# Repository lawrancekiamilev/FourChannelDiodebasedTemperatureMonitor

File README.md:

# FourChannelDiodebasedTemperatureMonitor
this project is a pcb and programing project. it is designed to be able to read the temperature of any diode based on its non ideal diode factor.  It is also designed to read an i2c EEPROM for serial identification and incorporates itself with a gui

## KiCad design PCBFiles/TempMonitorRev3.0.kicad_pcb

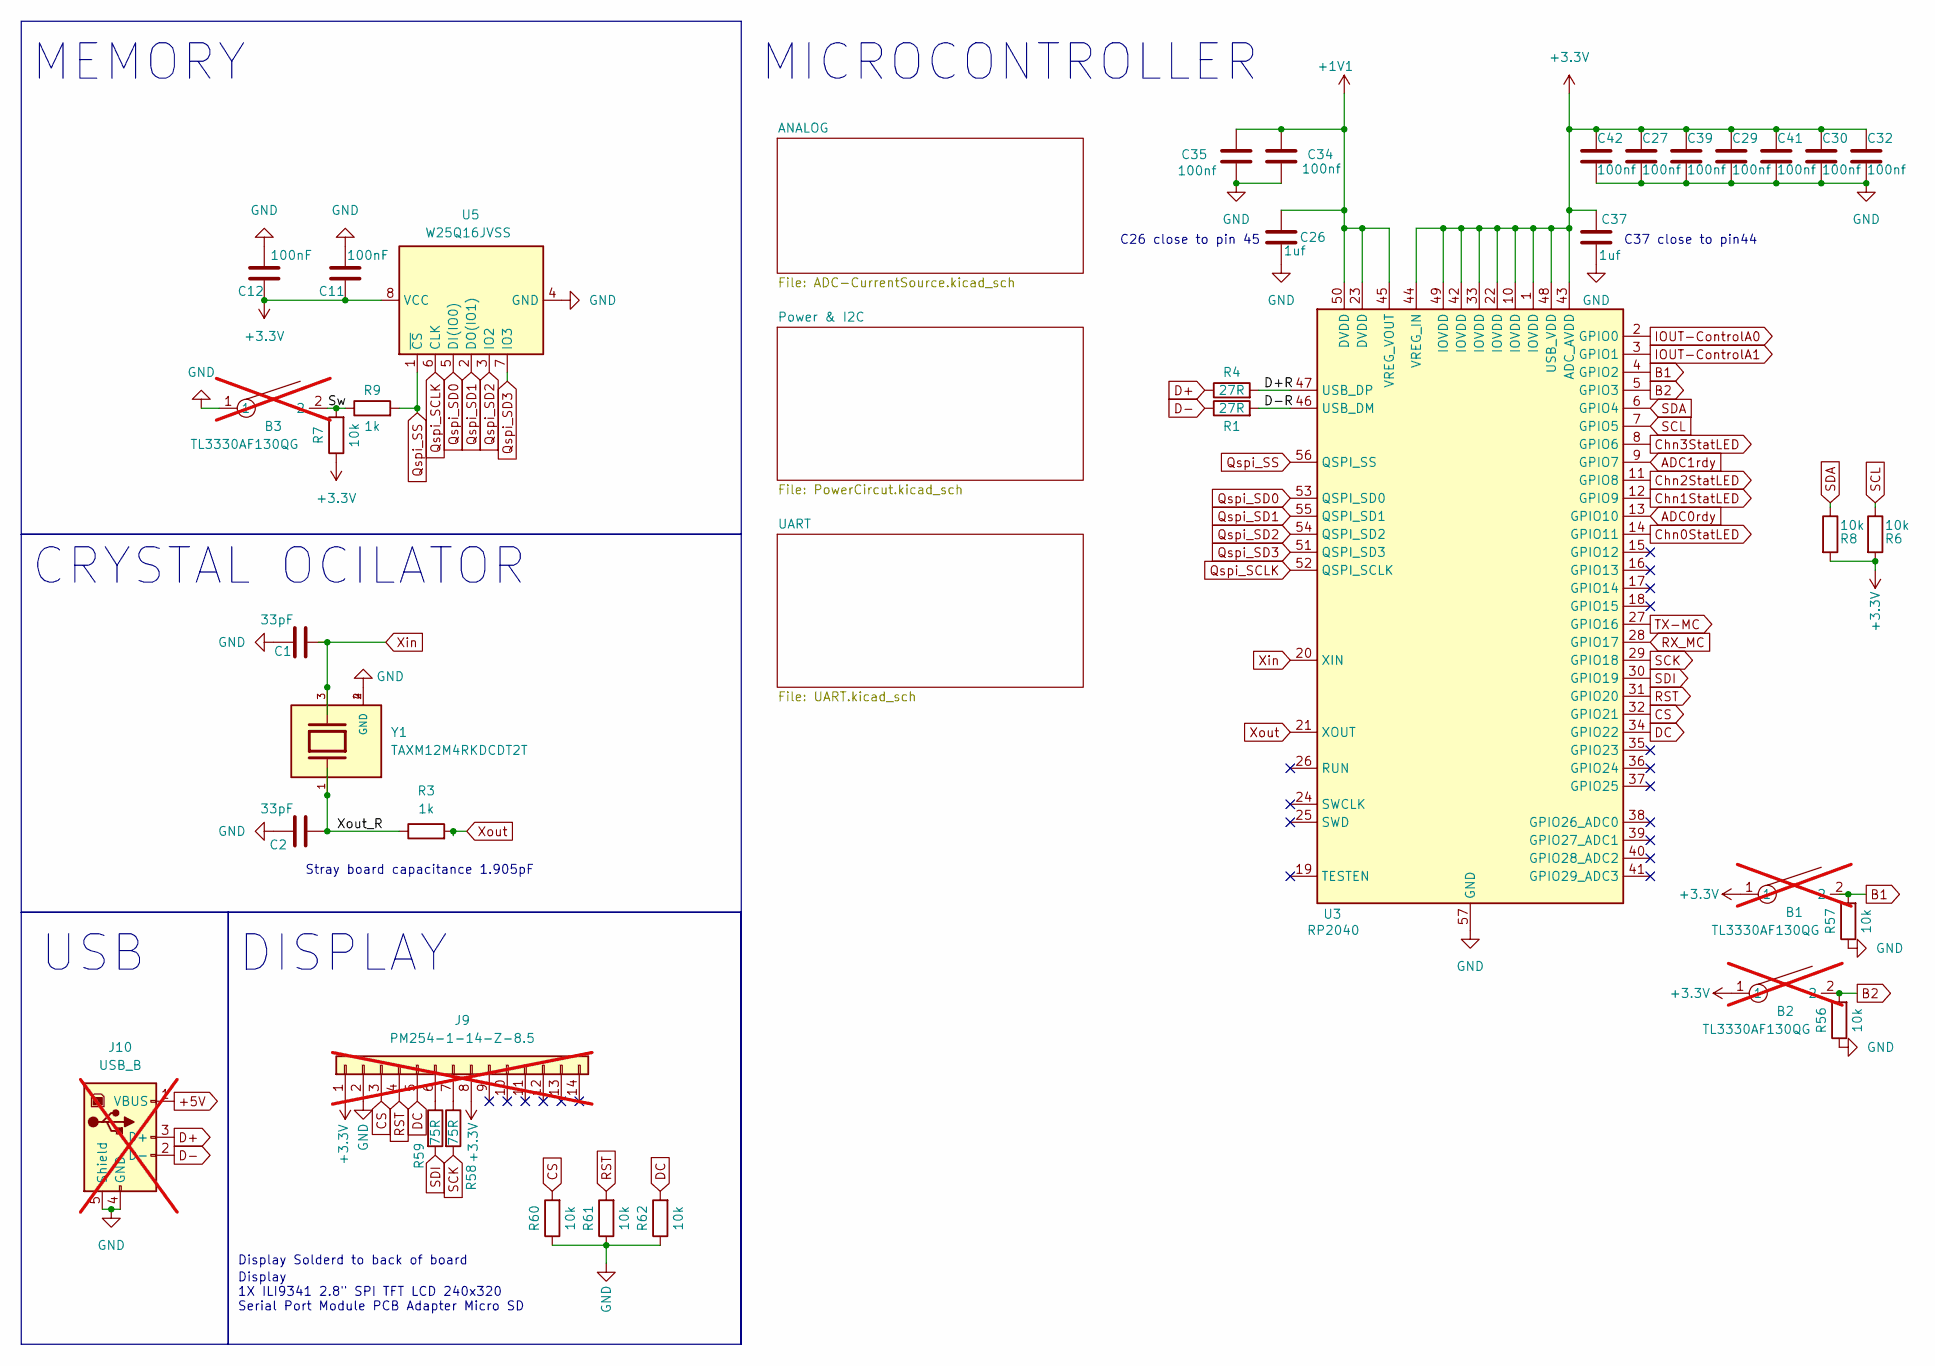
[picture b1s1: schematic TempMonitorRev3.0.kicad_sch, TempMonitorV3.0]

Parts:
B1, B2, B3: TL3330AF130QG; TL3330; JLC part # C2886885; not fitted
C1, C2: 33pF; C_0603_1608Metric; JLC part # C107047
C11, C12: 100nF; C_0603_1608Metric; JLC part # C14663
C26, C37: 1uf; C_0603_1608Metric; JLC part # C15849
C27, C29, C30, C32, C34, C35, C39, C41, C42: 100nf; C_0603_1608Metric; JLC part # C14663
J9: PM254-1-14-Z-8.5; PinSocket_1x14_P2.54mm_Vertical; JLC part # C2897377; not fitted
J10: USB_B; USB_B_OST_USB-B1HSxx_Horizontal; JLC part # C46392; not fitted
R1, R4: 27R; R_0603_1608Metric; JLC part # C25190
R3, R9: 1k; R_0603_1608Metric; JLC part # C21190
R6, R7, R8, R56, R57, R60, R61, R62: 10k; R_0603_1608Metric; JLC part # C25804
R58, R59: 75R; R_0603_1608Metric; JLC part # C25133
U3: RP2040; QFN-56-1EP_7x7mm_P0.4mm_EP3.2x3.2mm_ThermalVias; JLC part # C2040
U5: W25Q16JVSS; SOIC-8_5.3x5.3mm_P1.27mm; JLC part # C131025
Y1: TAXM12M4RKDCDT2T; Crystal_SMD_3225-4Pin_3.2x2.5mm; JLC part # C403945

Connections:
+1V1: C26.2, C34.1, C35.1, U3.23 (DVDD), U3.45 (VREG_VOUT), U3.50 (DVDD)
+3.3V: B1.1, B2.1, C11.1, C12.1, C27.1, C29.1, C30.1, C32.1, C37.2, C39.1, C41.1, C42.1, J9.1, J9.8, R6.2, R7.1, R8.2, U3.1 (IOVDD), U3.10 (IOVDD), U3.22 (IOVDD), U3.33 (IOVDD), U3.42 (IOVDD), U3.43 (ADC_AVDD), U3.44 (VREG_IN), U3.48 (USB_VDD), U3.49 (IOVDD), U5.8 (VCC); also elsewhere on the board
+5V: J10.1 (VBUS); also elsewhere on the board
/D+R: R4.2, U3.47 (USB_DP)
/D-R: R1.2, U3.46 (USB_DM)
/Sw: B3.2, R7.2, R9.1
/Xout_R: C2.1, R3.1, Y1.1
ADC0rdy: U3.13 (GPIO10); also elsewhere on the board
ADC1rdy: U3.9 (GPIO7); also elsewhere on the board
B1: B1.2, R57.2, U3.4 (GPIO2)
B2: B2.2, R56.2, U3.5 (GPIO3)
CS: J9.3, R60.2, U3.32 (GPIO21)
Chn0StatLED: U3.14 (GPIO11); also elsewhere on the board
Chn1StatLED: U3.12 (GPIO9); also elsewhere on the board
Chn2StatLED: U3.11 (GPIO8); also elsewhere on the board
Chn3StatLED: U3.8 (GPIO6); also elsewhere on the board
D+: J10.3 (D+), R4.1
D-: J10.2 (D-), R1.1
DC: J9.5, R62.2, U3.34 (GPIO22)
GND: B3.1, C1.2, C2.2, C11.2, C12.2, C26.1, C27.2, C29.2, C30.2, C32.2, C34.2, C35.2, C37.1, C39.2, C41.2, C42.2, J9.2, J10.4 (GND), J10.5 (Shield), R56.1, R57.1, R60.1, R61.1, R62.1, U3.57 (GND), U5.4 (GND), Y1.2 (GND), Y1.4 (GND); also elsewhere on the board
IOUT-ControlA0: U3.2 (GPIO0); also elsewhere on the board
IOUT-ControlA1: U3.3 (GPIO1); also elsewhere on the board
unnamed: J9.6, R59.1
unnamed: J9.7, R58.1
Qspi_SCLK: U3.52 (QSPI_SCLK), U5.6 (CLK)
Qspi_SD0: U3.53 (QSPI_SD0), U5.5 (DI(IO0))
Qspi_SD1: U3.55 (QSPI_SD1), U5.2 (DO(IO1))
Qspi_SD2: U3.54 (QSPI_SD2), U5.3 (IO2)
Qspi_SD3: U3.51 (QSPI_SD3), U5.7 (IO3)
Qspi_SS: R9.2, U3.56 (QSPI_SS), U5.1 (~CS)
RST: J9.4, R61.2, U3.31 (GPIO20)
RX_MC: U3.28 (GPIO17); also elsewhere on the board
SCK: R58.2, U3.29 (GPIO18)
SCL: R6.1, U3.7 (GPIO5); also elsewhere on the board
SDA: R8.1, U3.6 (GPIO4); also elsewhere on the board
SDI: R59.2, U3.30 (GPIO19)
TX-MC: U3.27 (GPIO16); also elsewhere on the board
Xin: C1.1, U3.20 (XIN), Y1.3
Xout: R3.2, U3.21 (XOUT)

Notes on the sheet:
C37 close to pin44
CRYSTAL OCILATOR
MICROCONTROLLER
Stray board capacitance 1.905pF
MEMORY
DISPLAY
Display 1X ILI9341 2.8" SPI TFT LCD 240x320 Serial Port Module PCB Adapter Micro SD
Display Solderd to back of board
USB
C26 close to pin 45

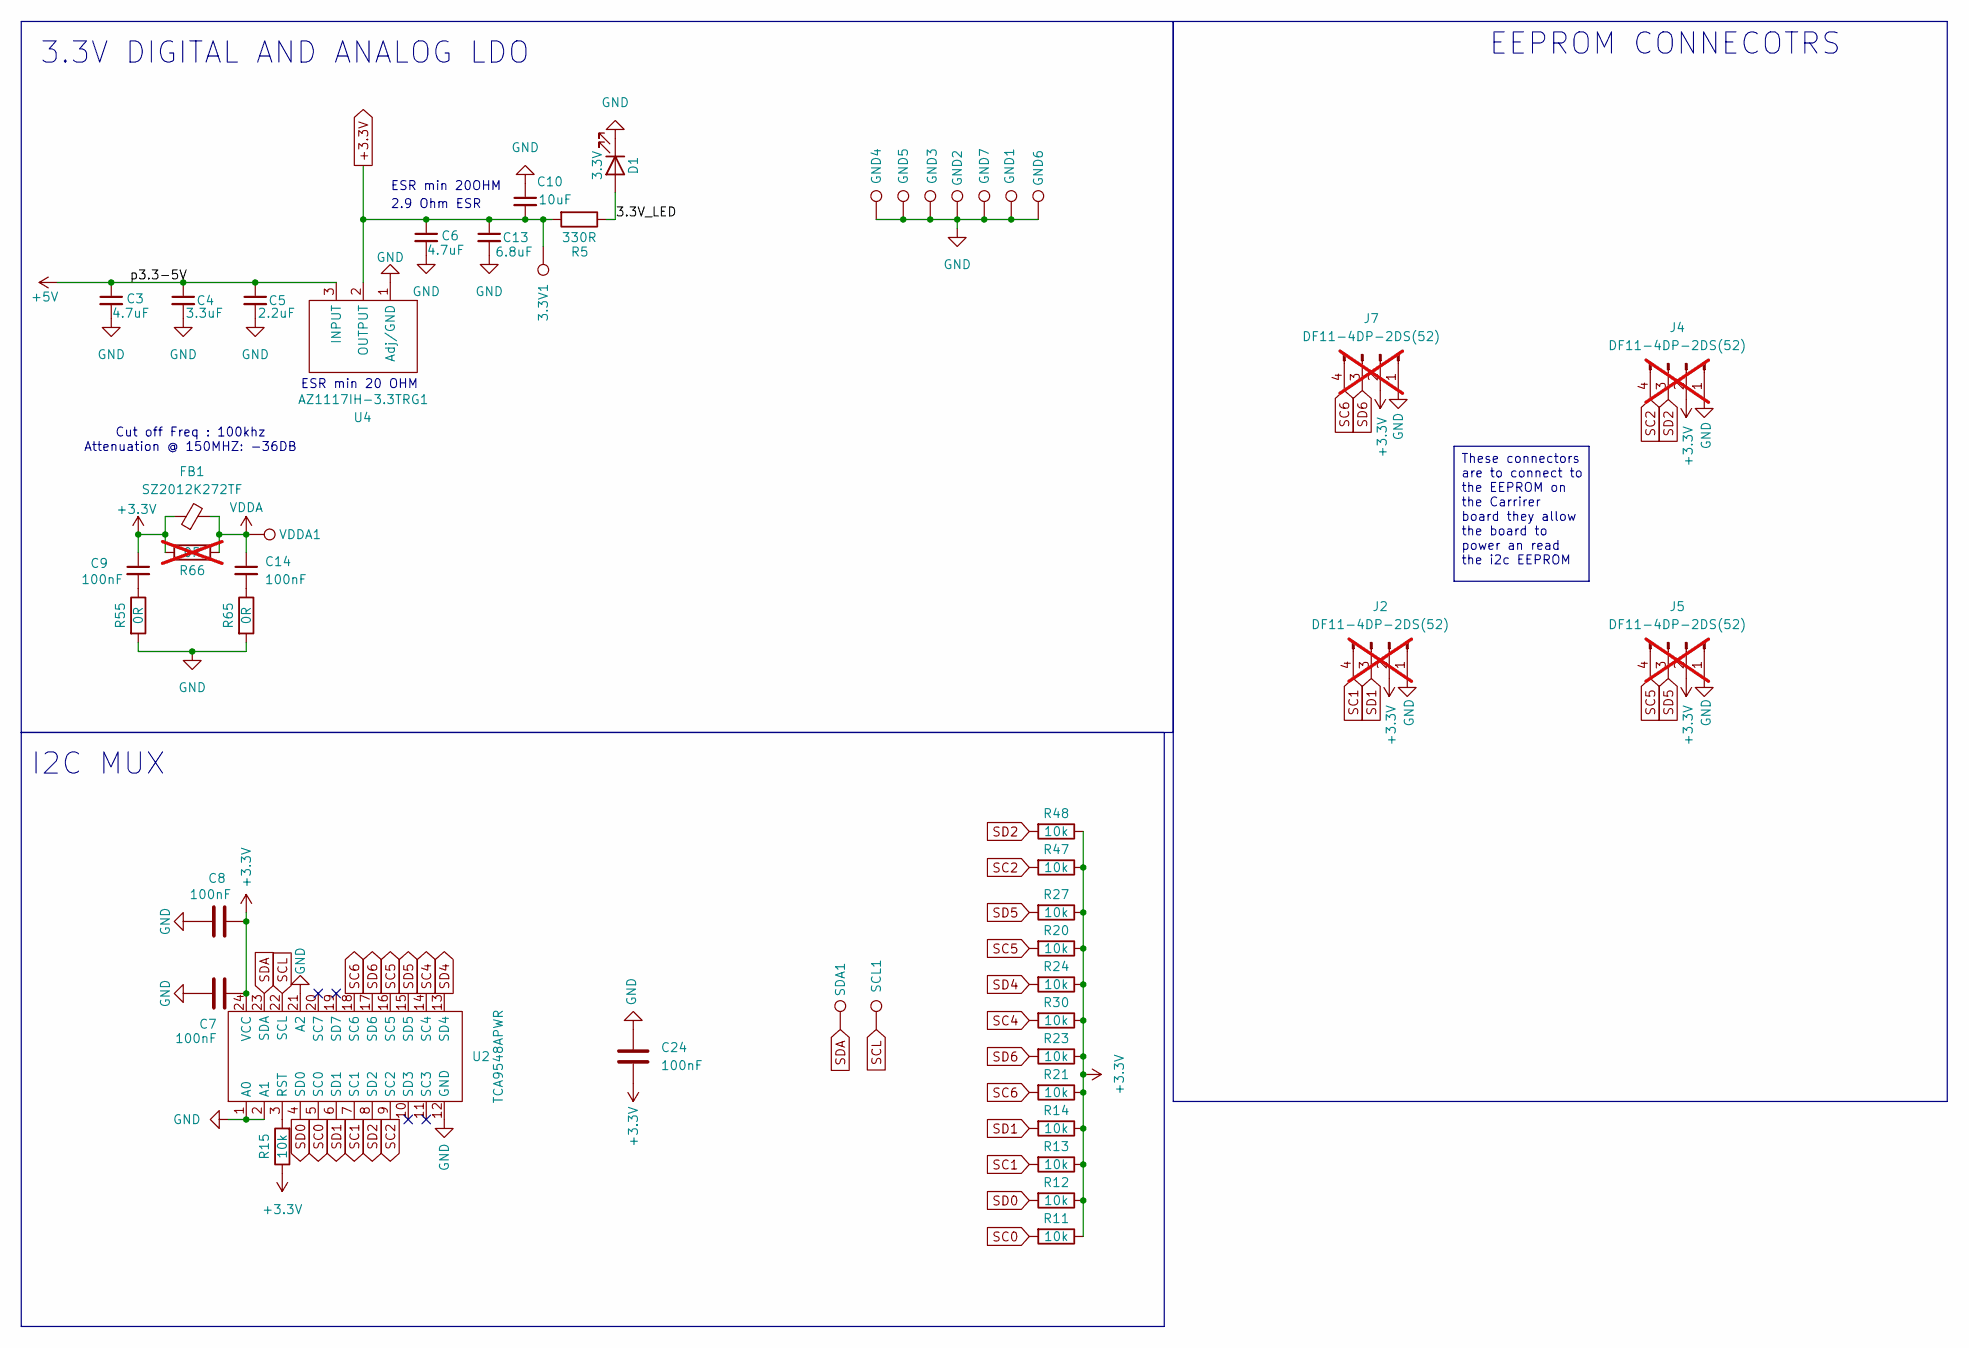
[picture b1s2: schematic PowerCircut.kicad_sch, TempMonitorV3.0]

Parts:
3.3V1: TestPoint; TestPoint_Pad_D1.5mm
C3, C6: 4.7uF; C_0805_2012Metric; JLC part # C1779
C4: 3.3uF; C_0805_2012Metric; JLC part # C7393948
C5: 2.2uF; C_0805_2012Metric; JLC part # C19110
C7, C8, C24: 100nF; C_0603_1608Metric; JLC part # C14663
C9, C14: 100nF; C_0805_2012Metric; JLC part # C49678
C10: 10uF; C_0805_2012Metric; JLC part # C5139488
C13: 6.8uF; C_0805_2012Metric; JLC part # C15850
D1: 3.3V; LED_0603_1608Metric_Pad1.05x0.95mm_HandSolder; JLC part # C19171390
FB1: SZ2012K272TF; R_0805_2012Metric; JLC part # C185876
GND1, GND2, GND3, GND4, GND5, GND6, GND7: TestPoint; TestPoint_Pad_D1.5mm
J2, J4, J5, J7: DF11-4DP-2DS(52); HRS_DF11-4DP-2DS_52_; not fitted
R5: 330R; R_0603_1608Metric; JLC part # C22775
R11, R12, R13, R14, R15, R20, R21, R23, R24, R27, R30, R47, R48: 10k; R_0603_1608Metric; JLC part # C25804
R55, R65: 0R; R_0603_1608Metric; JLC part # C21189
R66: 0R; R_0603_1608Metric; JLC part # C25804; not fitted
SCL1: TestPoint; TestPoint_Pad_D1.5mm
SDA1: TestPoint; TestPoint_Pad_D1.5mm
U2: TCA9548APWR; TCA9548A; JLC part # C130026
U4: AZ1117IH-3.3TRG1; AZ11171; JLC part # C108495
VDDA1: TestPoint; TestPoint_Pad_D1.5mm

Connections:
+3.3V: 3.3V1.1, C6.1, C7.2, C8.2, C9.1, C10.2, C13.1, C24.2, FB1.1, J2.2, J4.2, J5.2, J7.2, R5.2, R11.1, R12.1, R13.1, R14.1, R15.1, R20.1, R21.1, R23.1, R24.1, R27.1, R30.1, R47.1, R48.1, R66.1, U2.24 (VCC), U4.2 (OUTPUT); also elsewhere on the board
+5V: C3.1, C4.1, C5.1, U4.3 (INPUT); also elsewhere on the board
/Power & I2C/3.3V_LED: D1.2 (A), R5.1
GND: C3.2, C4.2, C5.2, C6.2, C7.1, C8.1, C10.1, C13.2, C24.1, D1.1 (K), GND1.1, GND2.1, GND3.1, GND4.1, GND5.1, GND6.1, GND7.1, J2.1, J4.1, J5.1, J7.1, R55.2, R65.2, U2.1 (A0), U2.2 (A1), U2.12 (GND), U2.21 (A2), U4.1 (Adj/GND); also elsewhere on the board
unnamed: C9.2, R55.1
unnamed: C14.2, R65.1
unnamed: R15.2, U2.3 (RST)
SC0: R11.2, U2.5 (SC0); also elsewhere on the board
SC1: J2.4, R13.2, U2.7 (SC1)
SC2: J4.4, R47.2, U2.9 (SC2)
SC4: R30.2, U2.14 (SC4); also elsewhere on the board
SC5: J5.4, R20.2, U2.16 (SC5)
SC6: J7.4, R21.2, U2.18 (SC6)
SCL: SCL1.1, U2.22 (SCL); also elsewhere on the board
SD0: R12.2, U2.4 (SD0); also elsewhere on the board
SD1: J2.3, R14.2, U2.6 (SD1)
SD2: J4.3, R48.2, U2.8 (SD2)
SD4: R24.2, U2.13 (SD4); also elsewhere on the board
SD5: J5.3, R27.2, U2.15 (SD5)
SD6: J7.3, R23.2, U2.17 (SD6)
SDA: SDA1.1, U2.23 (SDA); also elsewhere on the board
VDDA: C14.1, FB1.2, R66.2, VDDA1.1; also elsewhere on the board

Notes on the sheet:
Cut off Freq : 100khz Attenuation @ 150MHZ: -36DB
I2C MUX
3.3V DIGITAL AND ANALOG LDO
ESR min 20 OHM
2.9 Ohm ESR
EEPROM CONNECOTRS
ESR min 20OHM
These connectors are to connect to the EEPROM on the Carrirer board they allow the board to power an read the i2c EEPROM

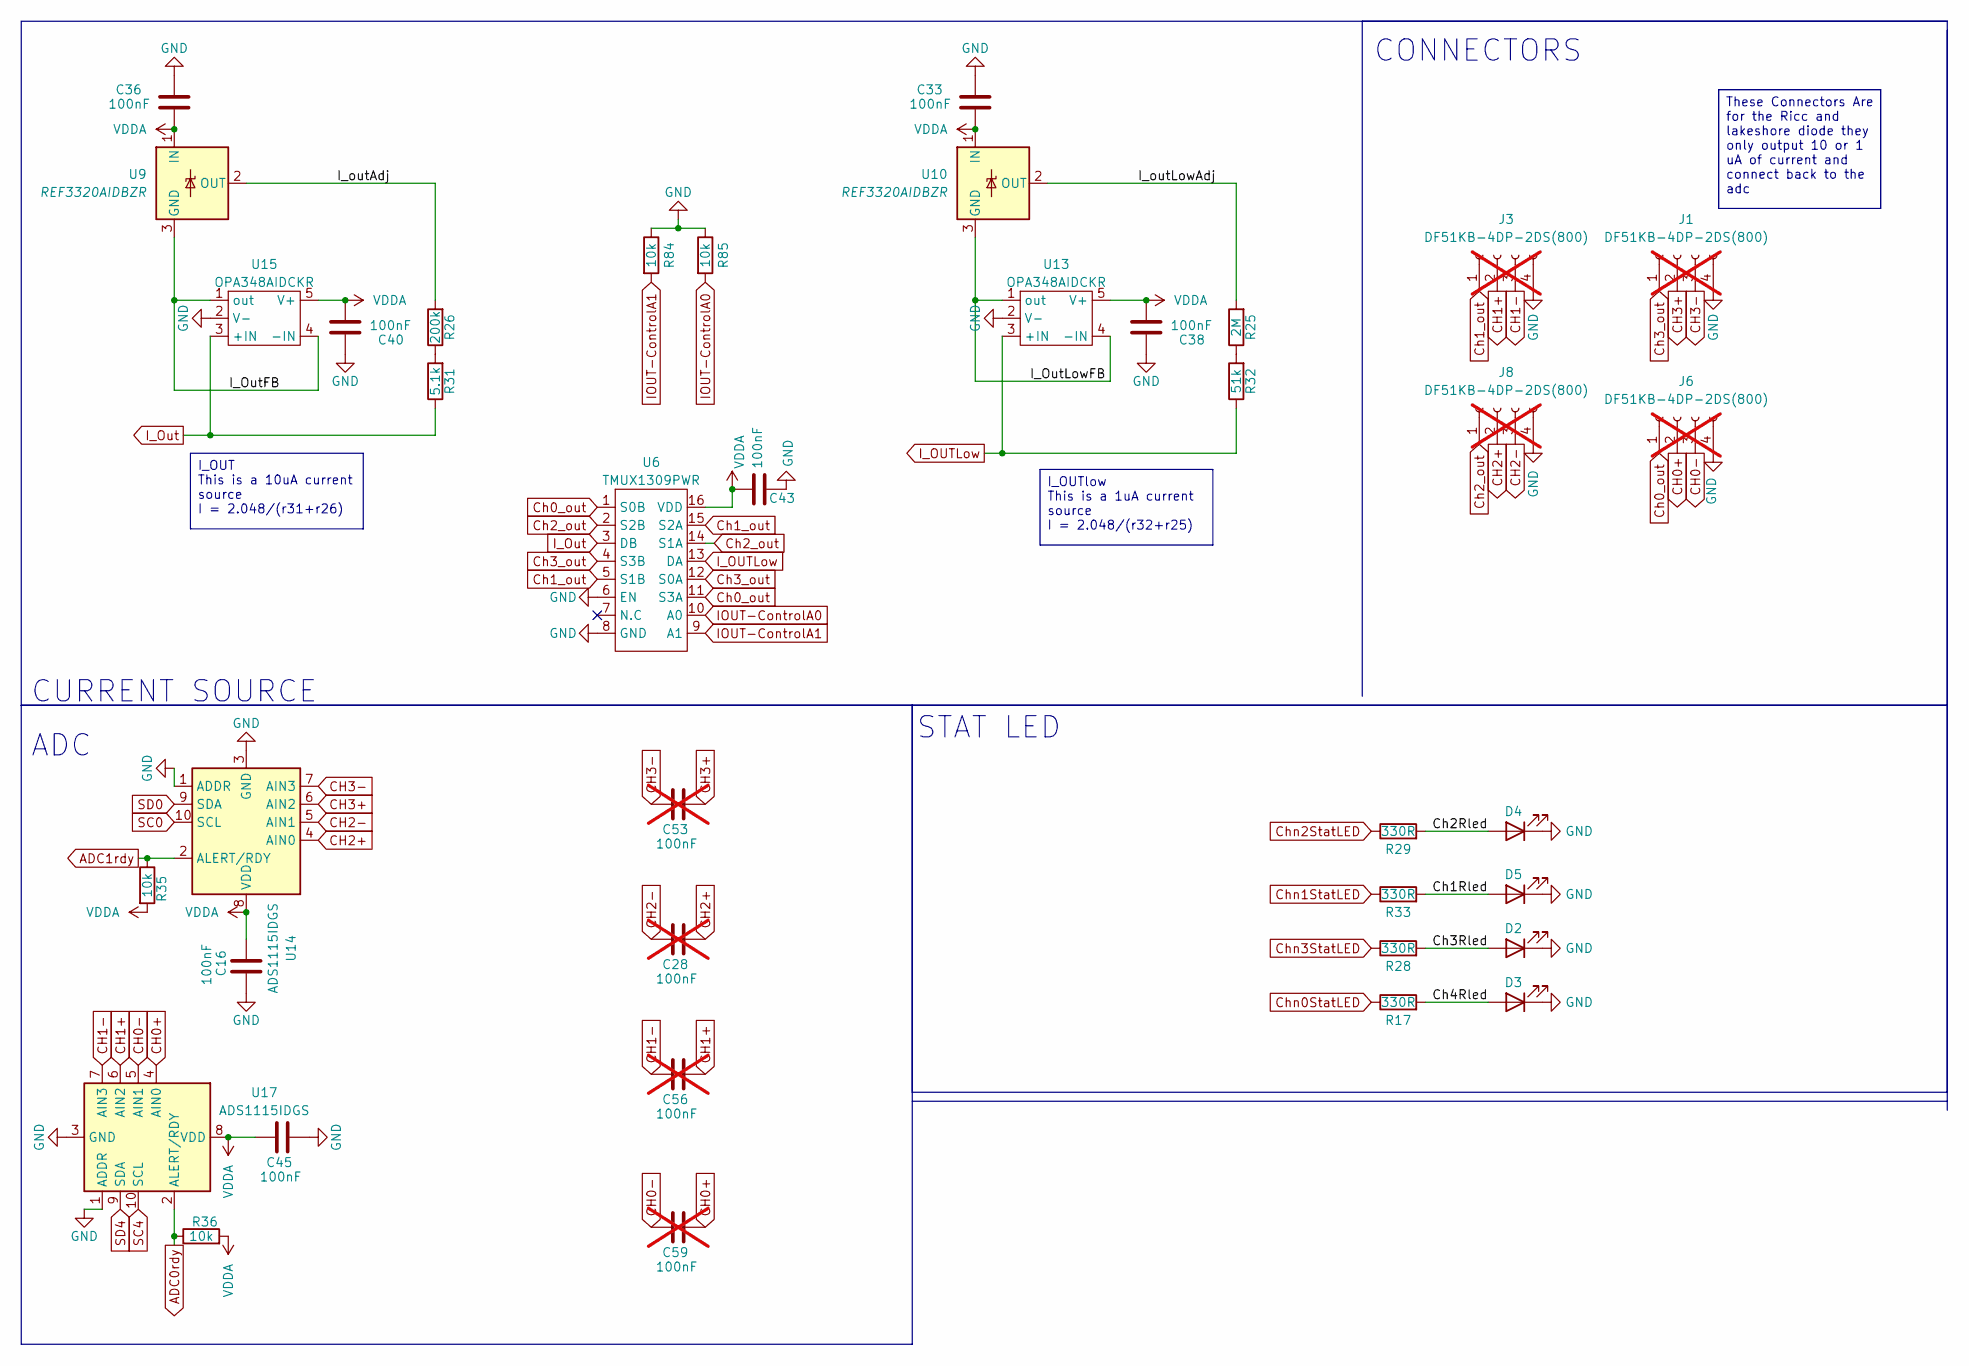
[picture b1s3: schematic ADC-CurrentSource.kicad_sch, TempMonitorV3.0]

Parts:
C16, C33, C36, C38, C40, C43, C45: 100nF; C_0603_1608Metric; JLC part # C14663
C28, C53, C56, C59: 100nF; C_0603_1608Metric; JLC part # C14663; not fitted
D2, D3, D4, D5: CN; LED_0603_1608Metric_Pad1.05x0.95mm_HandSolder; JLC part # C165981
J1, J3, J6, J8: DF51KB-4DP-2DS(800); DF51K-4DS-2C(800); not fitted
R17, R28, R29, R33: 330R; R_0603_1608Metric; JLC part # C22775
R25: 2M; R_0805_2012Metric; JLC part # C2984387
R26: 200k; R_0603_1608Metric; JLC part # C728585
R31: 5.1k; R_0603_1608Metric; JLC part # C122969
R32: 51k; R_0603_1608Metric; JLC part # C351642
R35, R36, R84, R85: 10k; R_0603_1608Metric; JLC part # C25804
U6: TMUX1309PWR; TSSOP-16_4.4x5mm_P0.65mm; JLC part # C2866286
U9, U10: REF3320AIDBZR; SOT-23; JLC part # C527421
U13, U15: OPA348AIDCKR; OPAx348; JLC part # C363280
U14, U17: ADS1115IDGS; TSSOP-10_3x3mm_P0.5mm; JLC part # C37593

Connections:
/ANALOG/Ch1Rled: D5.2 (A), R33.2
/ANALOG/Ch2Rled: D4.2 (A), R29.2
/ANALOG/Ch3Rled: D2.2 (A), R28.2
/ANALOG/Ch4Rled: D3.2 (A), R17.2
/ANALOG/I_OutFB: U9.3 (GND), U15.1 (out), U15.4 (-IN)
/ANALOG/I_OutLowFB: U10.3 (GND), U13.1 (out), U13.4 (-IN)
/ANALOG/I_outAdj: R26.2, U9.2 (OUT)
/ANALOG/I_outLowAdj: R25.2, U10.2 (OUT)
ADC0rdy: R36.1, U17.2 (ALERT/RDY); also elsewhere on the board
ADC1rdy: R35.1, U14.2 (ALERT/RDY); also elsewhere on the board
CH0+: C59.2, J6.2, U17.4 (AIN0)
CH0-: C59.1, J6.3, U17.5 (AIN1)
CH1+: C56.2, J3.2, U17.6 (AIN2)
CH1-: C56.1, J3.3, U17.7 (AIN3)
CH2+: C28.2, J8.2, U14.4 (AIN0)
CH2-: C28.1, J8.3, U14.5 (AIN1)
CH3+: C53.2, J1.2, U14.6 (AIN2)
CH3-: C53.1, J1.3, U14.7 (AIN3)
Ch0_out: J6.1, U6.1 (S0B), U6.11 (S3A)
Ch1_out: J3.1, U6.5 (S1B), U6.15 (S2A)
Ch2_out: J8.1, U6.2 (S2B), U6.14 (S1A)
Ch3_out: J1.1, U6.4 (S3B), U6.12 (S0A)
Chn0StatLED: R17.1; also elsewhere on the board
Chn1StatLED: R33.1; also elsewhere on the board
Chn2StatLED: R29.1; also elsewhere on the board
Chn3StatLED: R28.1; also elsewhere on the board
GND: C16.2, C33.1, C36.1, C38.1, C40.1, C43.1, C45.2, D2.1 (K), D3.1 (K), D4.1 (K), D5.1 (K), J1.4, J3.4, J6.4, J8.4, R84.1, R85.1, U6.6 (EN), U6.8 (GND), U13.2 (V-), U14.1 (ADDR), U14.3 (GND), U15.2 (V-), U17.1 (ADDR), U17.3 (GND); also elsewhere on the board
IOUT-ControlA0: R85.2, U6.10 (A0); also elsewhere on the board
IOUT-ControlA1: R84.2, U6.9 (A1); also elsewhere on the board
I_OUTLow: R32.1, U6.13 (DA), U13.3 (+IN)
I_Out: R31.1, U6.3 (DB), U15.3 (+IN)
unnamed: R25.1, R32.2
unnamed: R26.1, R31.2
SC0: U14.10 (SCL); also elsewhere on the board
SC4: U17.10 (SCL); also elsewhere on the board
SD0: U14.9 (SDA); also elsewhere on the board
SD4: U17.9 (SDA); also elsewhere on the board
VDDA: C16.1, C33.2, C36.2, C38.2, C40.2, C43.2, C45.1, R35.2, R36.2, U6.16 (VDD), U9.1 (IN), U10.1 (IN), U13.5 (V+), U14.8 (VDD), U15.5 (V+), U17.8 (VDD); also elsewhere on the board

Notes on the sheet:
CONNECTORS
ADC
STAT LED
CURRENT SOURCE
These Connectors Are for the Ricc and lakeshore diode they only output 10 or 1 uA of current and connect back to the adc
I_OUT This is a 10uA current source I = 2.048/(r31+r26)
I_OUTlow This is a 1uA current source I = 2.048/(r32+r25)

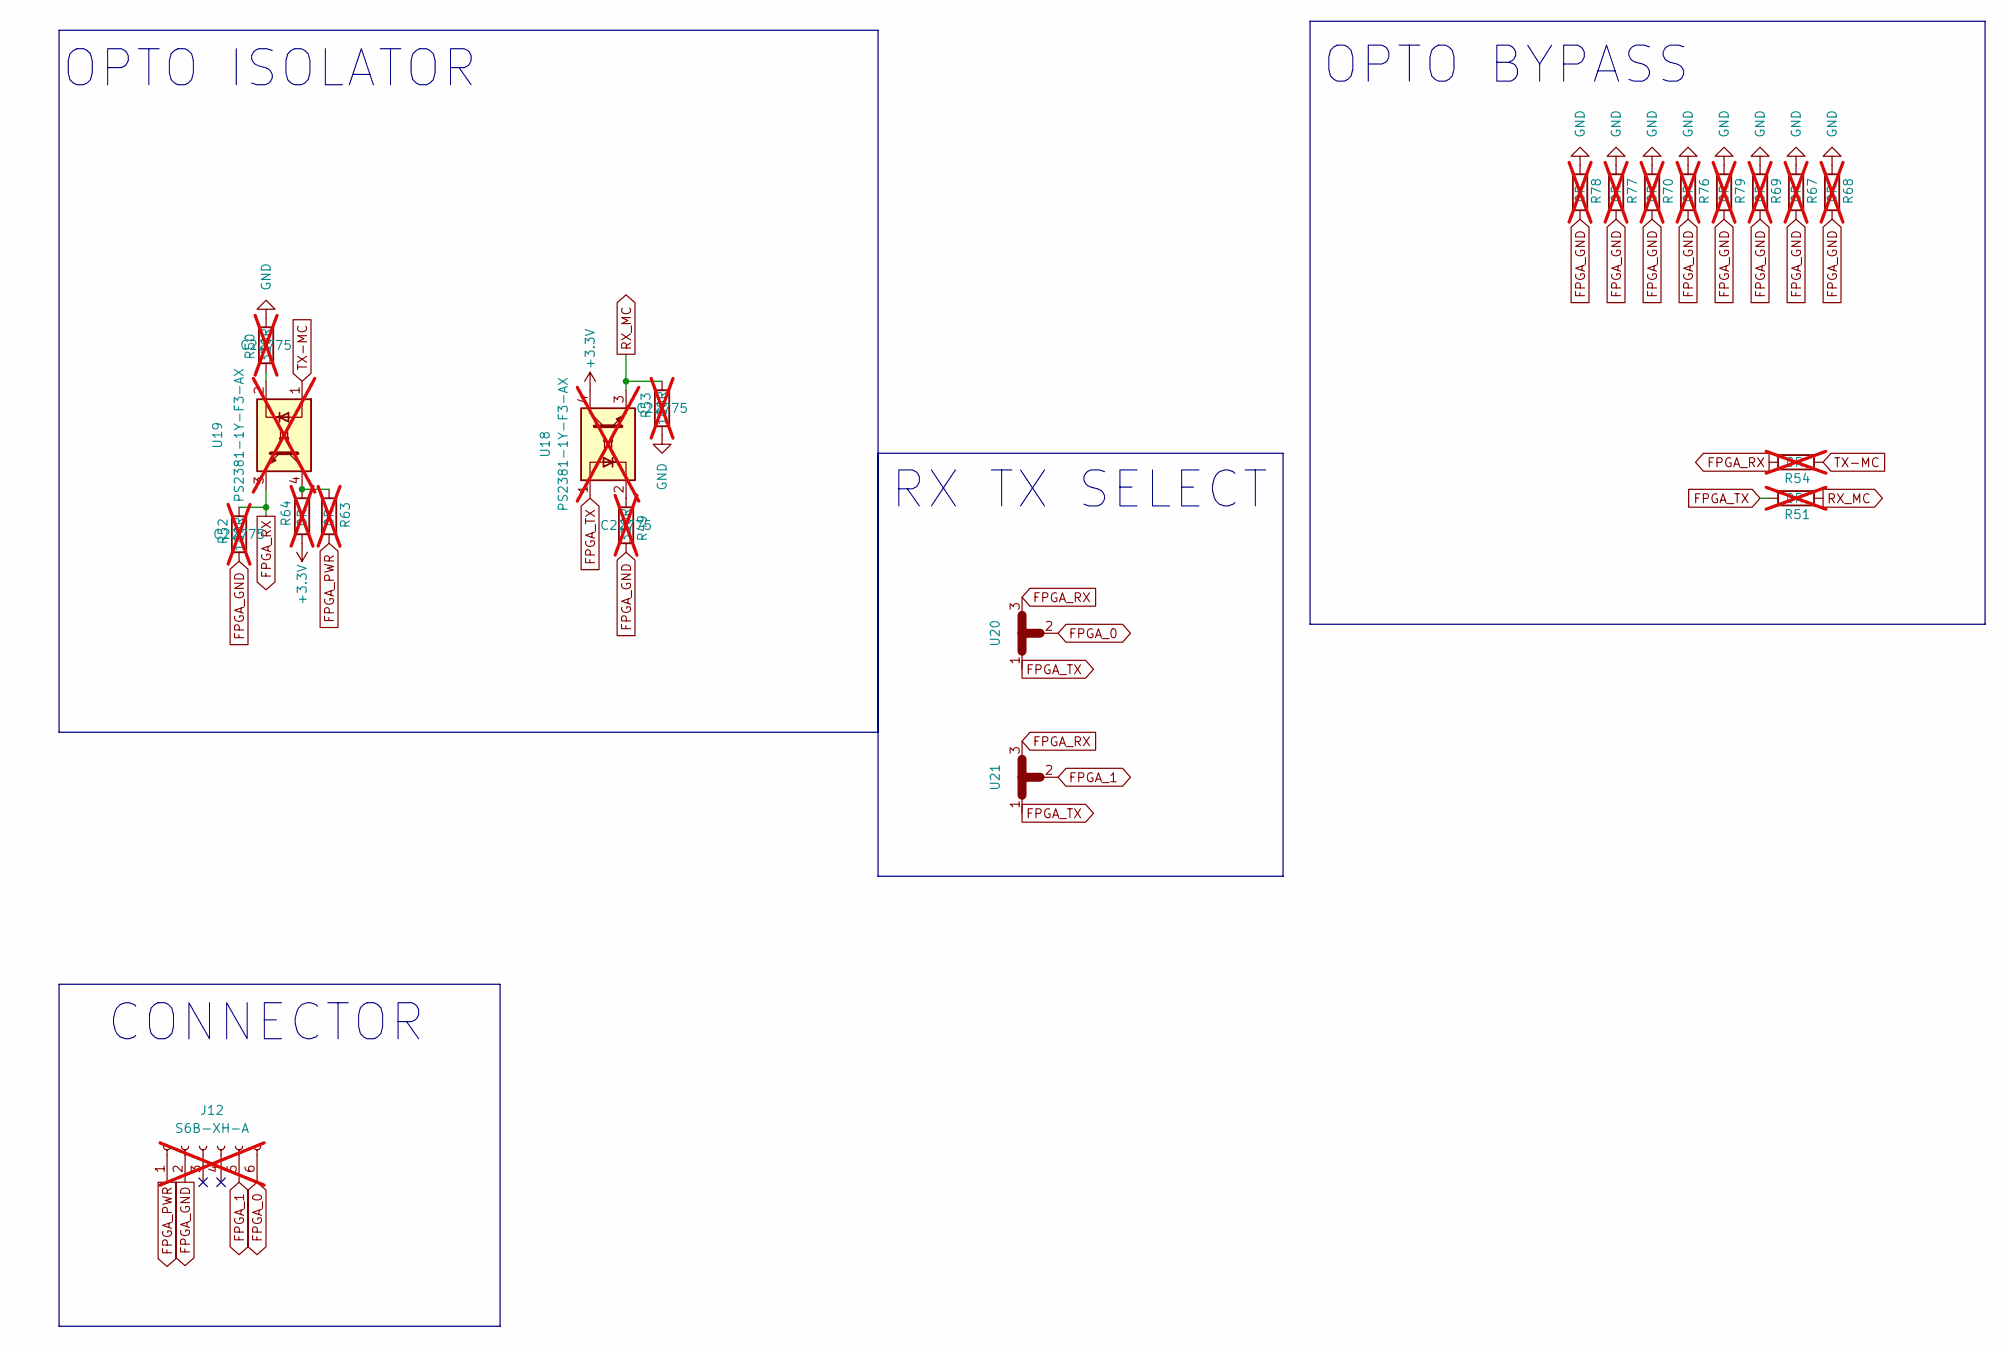
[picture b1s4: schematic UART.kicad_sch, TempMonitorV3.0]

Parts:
J12: S6B-XH-A; JST_EH_S6B-EH_1x06_P2.50mm_Horizontal; not fitted
R49, R50: 330R; R_0603_1608Metric; JLC part # C22775; not fitted
R51, R54, R67, R68, R69, R70, R76, R77, R78, R79: 0R; R_0805_2012Metric_Pad1.20x1.40mm_HandSolder; not fitted
R52, R53: 100R; R_0603_1608Metric; JLC part # C22775; not fitted
R63, R64: 0R; R_0603_1608Metric; not fitted
U18, U19: PS2381-1Y-F3-AX; LSOP-4 (2.54mm); not fitted
U20, U21: SolderJumper-3_P1.3mm_Open_RoundedPad1.0x1.5mm_NumberLabels

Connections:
+3.3V: R64.2, U18.4; also elsewhere on the board
FPGA_0: J12.6, U20.2
FPGA_1: J12.5, U21.2
FPGA_GND: J12.2, R49.1, R52.2, R67.2, R68.2, R69.2, R70.2, R76.2, R77.2, R78.2, R79.2
FPGA_PWR: J12.1, R63.2
FPGA_RX: R52.1, R54.2, U19.3, U20.3, U21.3
FPGA_TX: R51.2, U18.1, U20.1, U21.1
GND: R50.2, R53.2, R67.1, R68.1, R69.1, R70.1, R76.1, R77.1, R78.1, R79.1; also elsewhere on the board
unnamed: R49.2, U18.2
unnamed: R50.1, U19.2
unnamed: R63.1, R64.1, U19.4
RX_MC: R51.1, R53.1, U18.3; also elsewhere on the board
TX-MC: R54.1, U19.1; also elsewhere on the board

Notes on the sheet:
RX TX SELECT
OPTO BYPASS
CONNECTOR
OPTO ISOLATOR

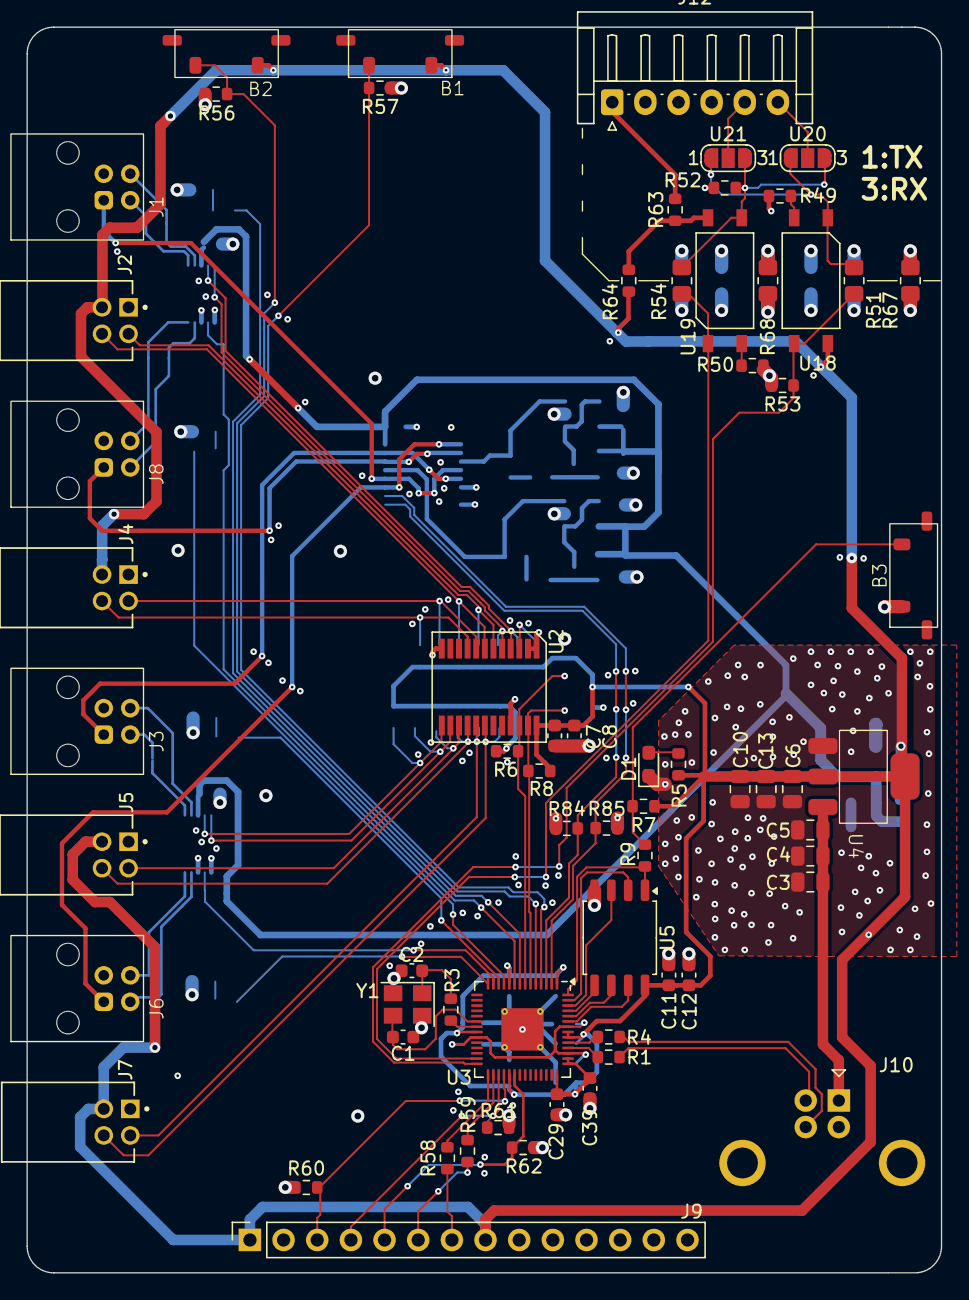
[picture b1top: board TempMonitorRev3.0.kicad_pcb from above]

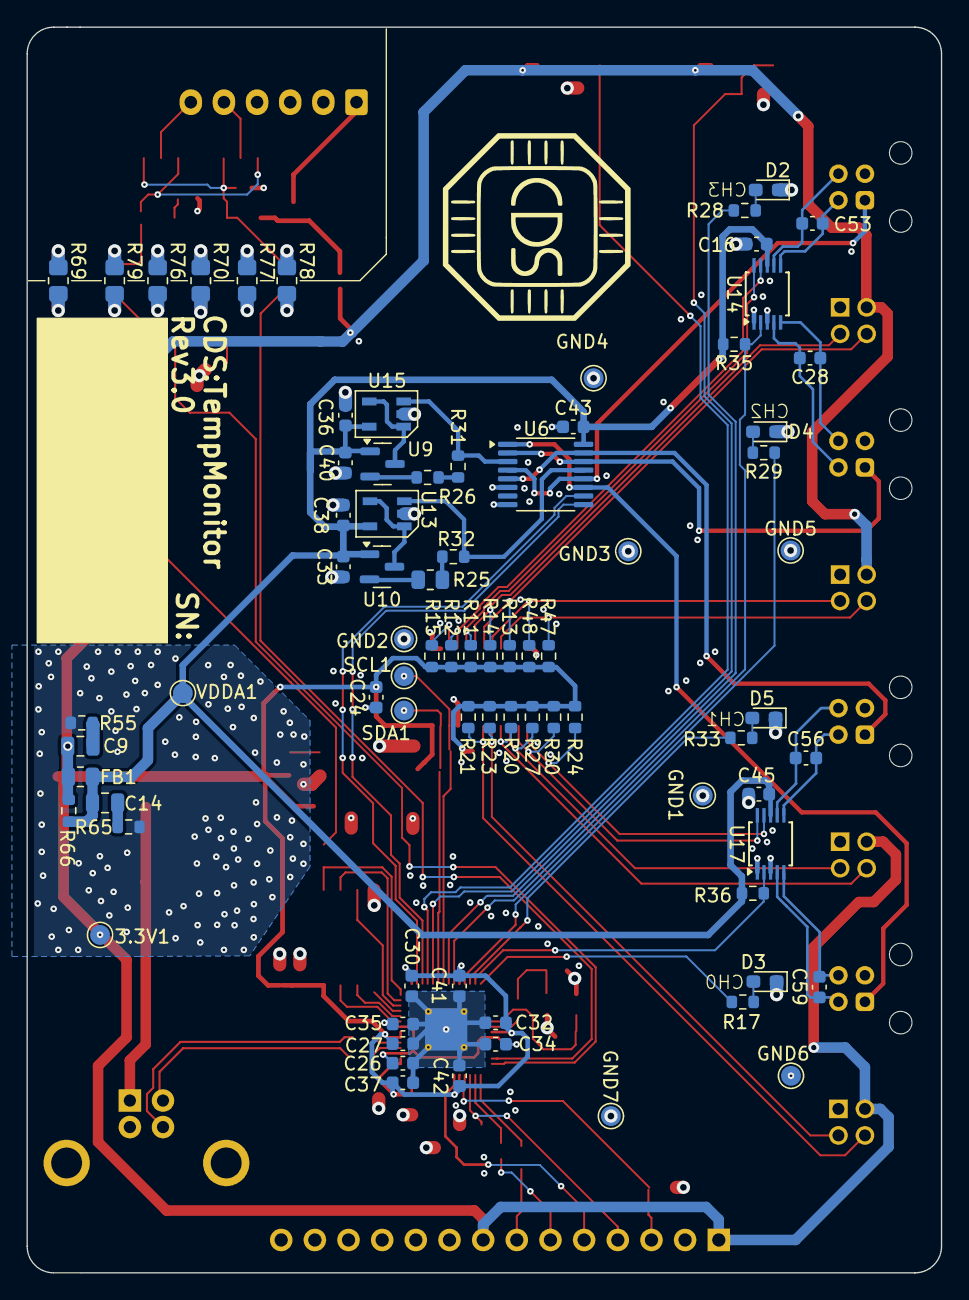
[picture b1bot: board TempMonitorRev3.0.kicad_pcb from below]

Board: 4 copper layers, 69.0 x 94.0 mm, 143 parts (78 on the bottom side), 89 nets.

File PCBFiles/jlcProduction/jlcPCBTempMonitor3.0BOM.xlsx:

Comment | Designator | FootPrint | JLCPCB PART#
TAXM12M4RKDCDT2T | Y1 | Crystal:Crystal_SMD_3225-4Pin_3.2x2.5mm | C403945
ADS1115IDGS | U14, U17 | Package_SO:TSSOP-10_3x3mm_P0.5mm | C37593
OPA348AIDCKR | U13, U15 | LawranceUserLib:OPAx348 | C363280
REF3320AIDBZR | U9, U10 | Package_TO_SOT_SMD:SOT-23 | C527421
TMUX1309PWR | U6 | Package_SO:TSSOP-16_4.4x5mm_P0.65mm | C2866286
W25Q16JVSS | U5 | Package_SO:SOIC-8_5.3x5.3mm_P1.27mm | C131025
AZ1117IH-3.3TRG1 | U4 | LawranceUserLib:AZ11171 | C108495
RP2040 | U3 | Package_DFN_QFN:QFN-56-1EP_7x7mm_P0.4mm_EP3.2x3.2mm_ThermalVias | C2040
TCA9548APWR | U2 | LawranceUserLib:TCA9548A | C130026
75R | R58, R59 | Resistor_SMD:R_0603_1608Metric | C25133
0R | R55, R65 | Resistor_SMD:R_0603_1608Metric | C21189
51k | R32 | Resistor_SMD:R_0603_1608Metric | C351642
5.1k | R31 | Resistor_SMD:R_0603_1608Metric | C122969
200k | R26 | Resistor_SMD:R_0603_1608Metric | C728585
2M | R25 | Resistor_SMD:R_0805_2012Metric | C2984387
10k | R6,R7,R8,R11,R12,R13,R14,R15,R20,R21,R23,R24,R27,R30,R35,R36,R47,R48,R56,R57,R6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 | Resistor_SMD:R_0603_1608Metric | C25804
330R | R5, R17, R28, R29, R33 | Resistor_SMD:R_0603_1608Metric | C22775
1k | R3, R9 | Resistor_SMD:R_0603_1608Metric | C21190
27R | R1, R4 | Resistor_SMD:R_0603_1608Metric | C25190
SZ2012K272TF | FB1 | Resistor_SMD:R_0805_2012Metric | C185876
CN | D2,D3,D4,D5 | LED_SMD:LED_0603_1608Metric_Pad1.05x0.95mm_HandSolder | C165981
3.3V | D1 | LED_SMD:LED_0603_1608Metric_Pad1.05x0.95mm_HandSolder | C19171390
100nf | C27, C29, C30, C32, C34, C35, C39, C41, C42 | Capacitor_SMD:C_0603_1608Metric | C14663
1uf | C26, C37 | Capacitor_SMD:C_0603_1608Metric | C15849
6.8uF | C13 | Capacitor_SMD:C_0805_2012Metric | C15850
10uF | C10 | Capacitor_SMD:C_0805_2012Metric | C5139488
100nF | C9,C14 | Capacitor_SMD:C_0805_2012Metric | C49678
100nF | C7,C8,C11,C12,C16,C24,C33,C36,C38,C40,C43,C45 | Capacitor_SMD:C_0603_1608Metric | C14663
2.2uF | C5 | Capacitor_SMD:C_0805_2012Metric | C19110
3.3uF | C4 | Capacitor_SMD:C_0805_2012Metric | C7393948
4.7uF | C3, C6 | Capacitor_SMD:C_0805_2012Metric | C1779
33pF | C1, C2 | Capacitor_SMD:C_0603_1608Metric | C107047
